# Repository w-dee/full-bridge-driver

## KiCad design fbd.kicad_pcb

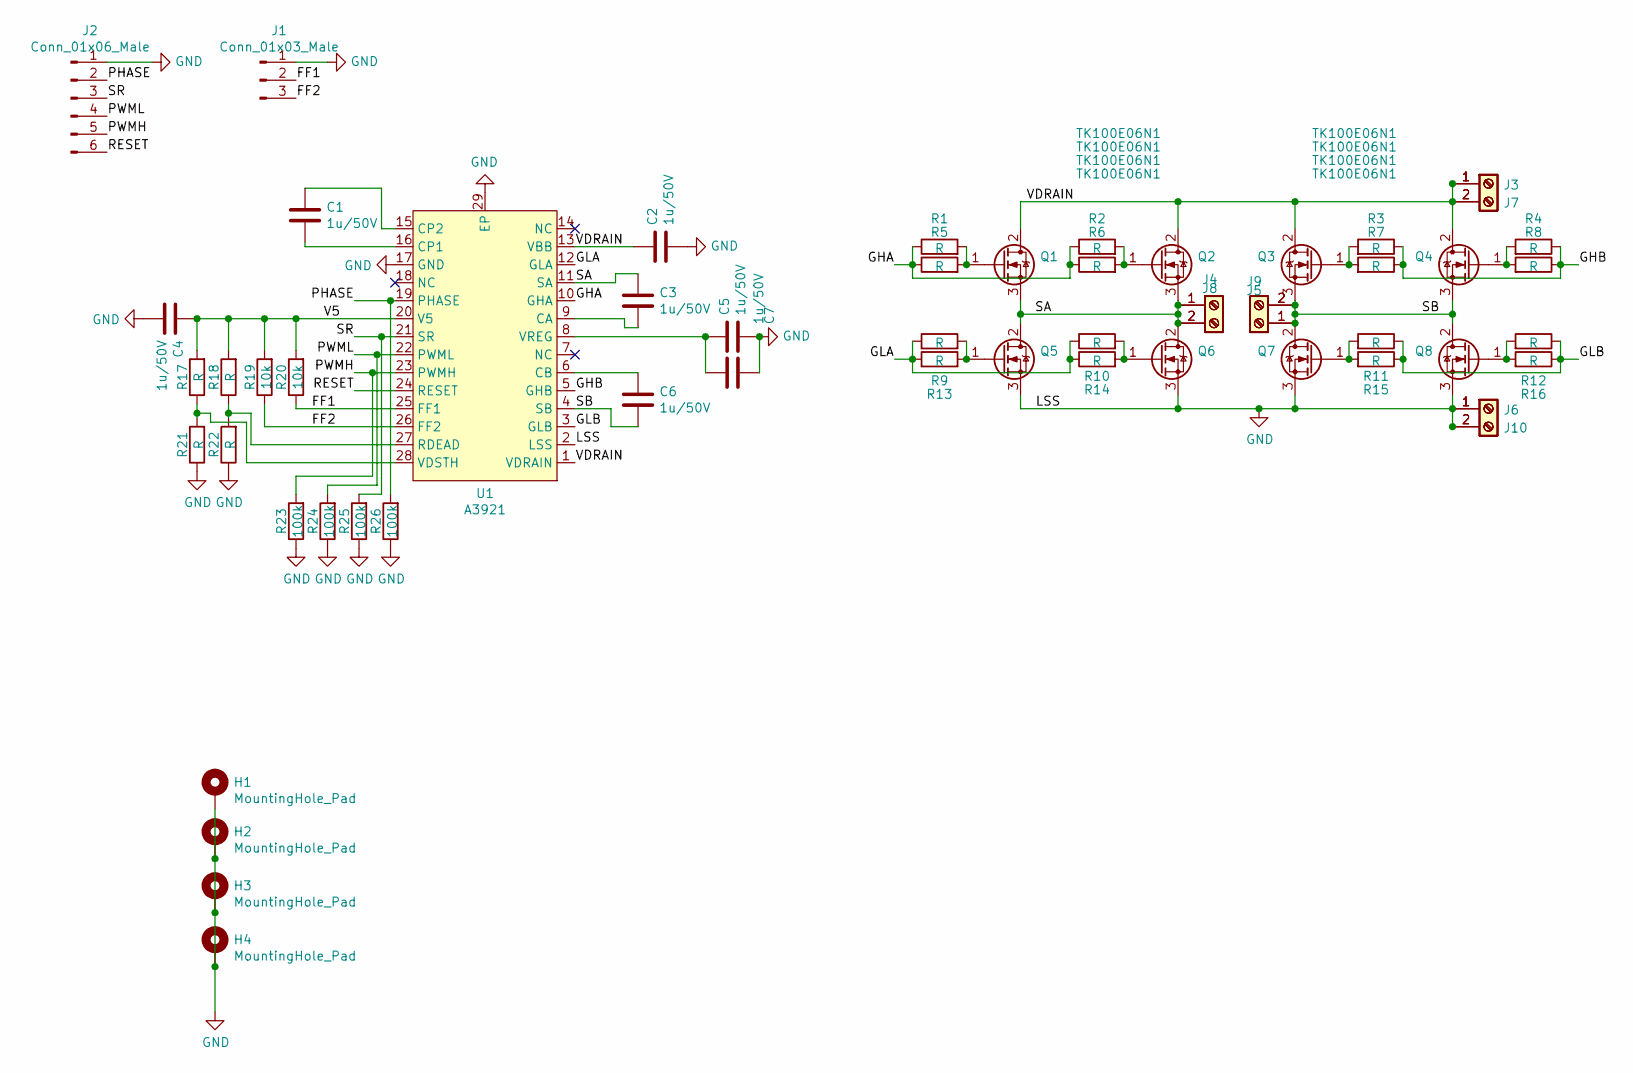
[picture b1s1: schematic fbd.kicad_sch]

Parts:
C1, C2, C3, C4, C5, C6, C7: 1u/50V; R_0603_1608Metric_Pad0.98x0.95mm_HandSolder
H1, H2, H3, H4: MountingHole_Pad; MountingHole_3.2mm_M3
J1: Conn_01x03_Male; JST_XH_B3B-XH-A_1x03_P2.50mm_Vertical
J2: Conn_01x06_Male; JST_XH_B6B-XH-A_1x06_P2.50mm_Vertical
J3, J4, J5, J6, J7, J8, J9, J10: Screw_Terminal_01x02; Terminal-Block-7.62mm-20A-300V
Q1, Q2, Q3, Q4, Q5, Q6, Q7, Q8: TK100E06N1; TO-252-3_Heatsink-TO220-Compat
R1, R2, R3, R4, R5, R6, R7, R8, R9, R10, R11, R12, R13, R14, R15, R16, R17, R18, R21, R22: R; R_0603_1608Metric_Pad0.98x0.95mm_HandSolder
R19, R20: 10k; R_0603_1608Metric_Pad0.98x0.95mm_HandSolder
R23, R24, R25, R26: 100k; R_0603_1608Metric_Pad0.98x0.95mm_HandSolder
U1: A3921; TSSOP-28-1EP_4.4x9.7mm-pin-width6.1_P0.65mm

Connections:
/FF1: J1.2, R20.1, U1.25 (FF1)
/FF2: J1.3, R19.1, U1.26 (FF2)
/GHA: R1.1, R2.1, R5.1, R6.1, U1.10 (GHA)
/GHB: R3.1, R4.1, R7.1, R8.1, U1.5 (GHB)
/GLA: R9.1, R10.1, R13.1, R14.1, U1.12 (GLA)
/GLB: R11.1, R12.1, R15.1, R16.1, U1.3 (GLB)
/PHASE: J2.2, R26.2, U1.19 (PHASE)
/PWMH: J2.5, R23.2, U1.23 (PWMH)
/PWML: J2.4, R24.2, U1.22 (PWML)
/RESET: J2.6, U1.24 (RESET)
/SA: C3.1, J4.1, J4.2, J8.1, J8.2, Q1.3 (S), Q2.3 (S), Q5.2 (D), Q6.2 (D), U1.11 (SA)
/SB: C6.2, J5.1, J5.2, J9.1, J9.2, Q3.3 (S), Q4.3 (S), Q7.2 (D), Q8.2 (D), U1.4 (SB)
/SR: J2.3, R25.2, U1.21 (SR)
/V5: C4.1, R17.2, R18.2, R19.2, R20.2, U1.20 (V5)
/VDRAIN: C2.1, J3.1, J3.2, J7.1, J7.2, Q1.2 (D), Q2.2 (D), Q3.2 (D), Q4.2 (D), U1.1 (VDRAIN), U1.13 (VBB)
GND: C2.2, C4.2, C5.2, C7.2, H1.1, H2.1, H3.1, H4.1, J1.1, J2.1, J6.1, J6.2, J10.1, J10.2, Q5.3 (S), Q6.3 (S), Q7.3 (S), Q8.3 (S), R21.1, R22.1, R23.1, R24.1, R25.1, R26.1, U1.2 (LSS), U1.17 (GND), U1.29 (EP)
unnamed: C1.1, U1.15 (CP2)
unnamed: C1.2, U1.16 (CP1)
unnamed: C3.2, U1.9 (CA)
unnamed: C5.1, C7.1, U1.8 (VREG)
unnamed: C6.1, U1.6 (CB)
unnamed: Q1.1 (G), R1.2, R5.2
unnamed: Q2.1 (G), R2.2, R6.2
unnamed: Q3.1 (G), R3.2, R7.2
unnamed: Q4.1 (G), R4.2, R8.2
unnamed: Q5.1 (G), R9.2, R13.2
unnamed: Q6.1 (G), R10.2, R14.2
unnamed: Q7.1 (G), R11.2, R15.2
unnamed: Q8.1 (G), R12.2, R16.2
unnamed: R17.1, R21.2, U1.28 (VDSTH)
unnamed: R18.1, R22.2, U1.27 (RDEAD)

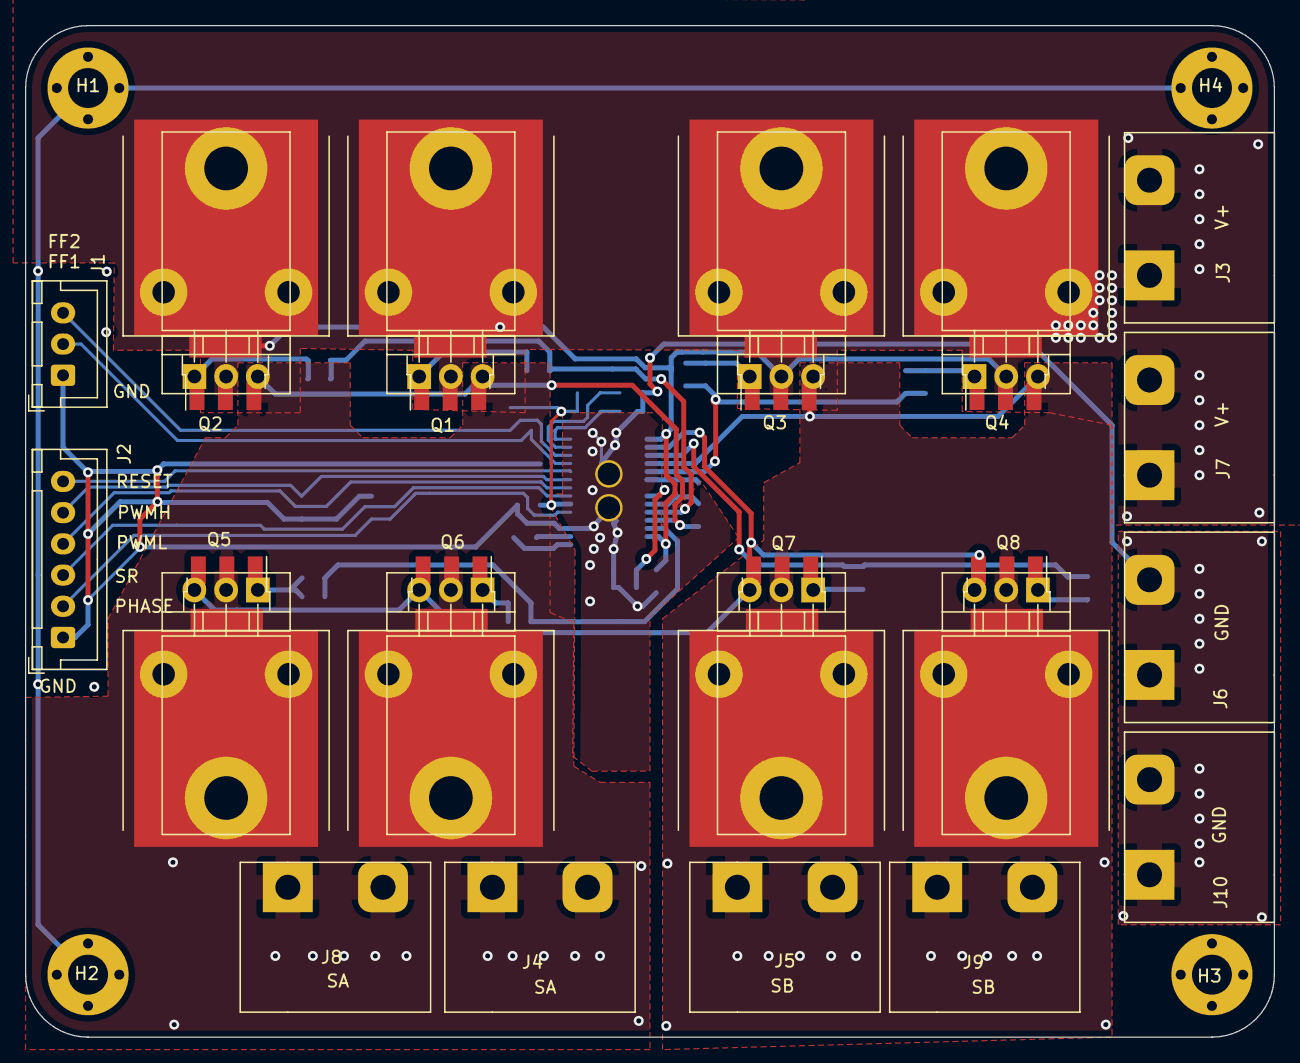
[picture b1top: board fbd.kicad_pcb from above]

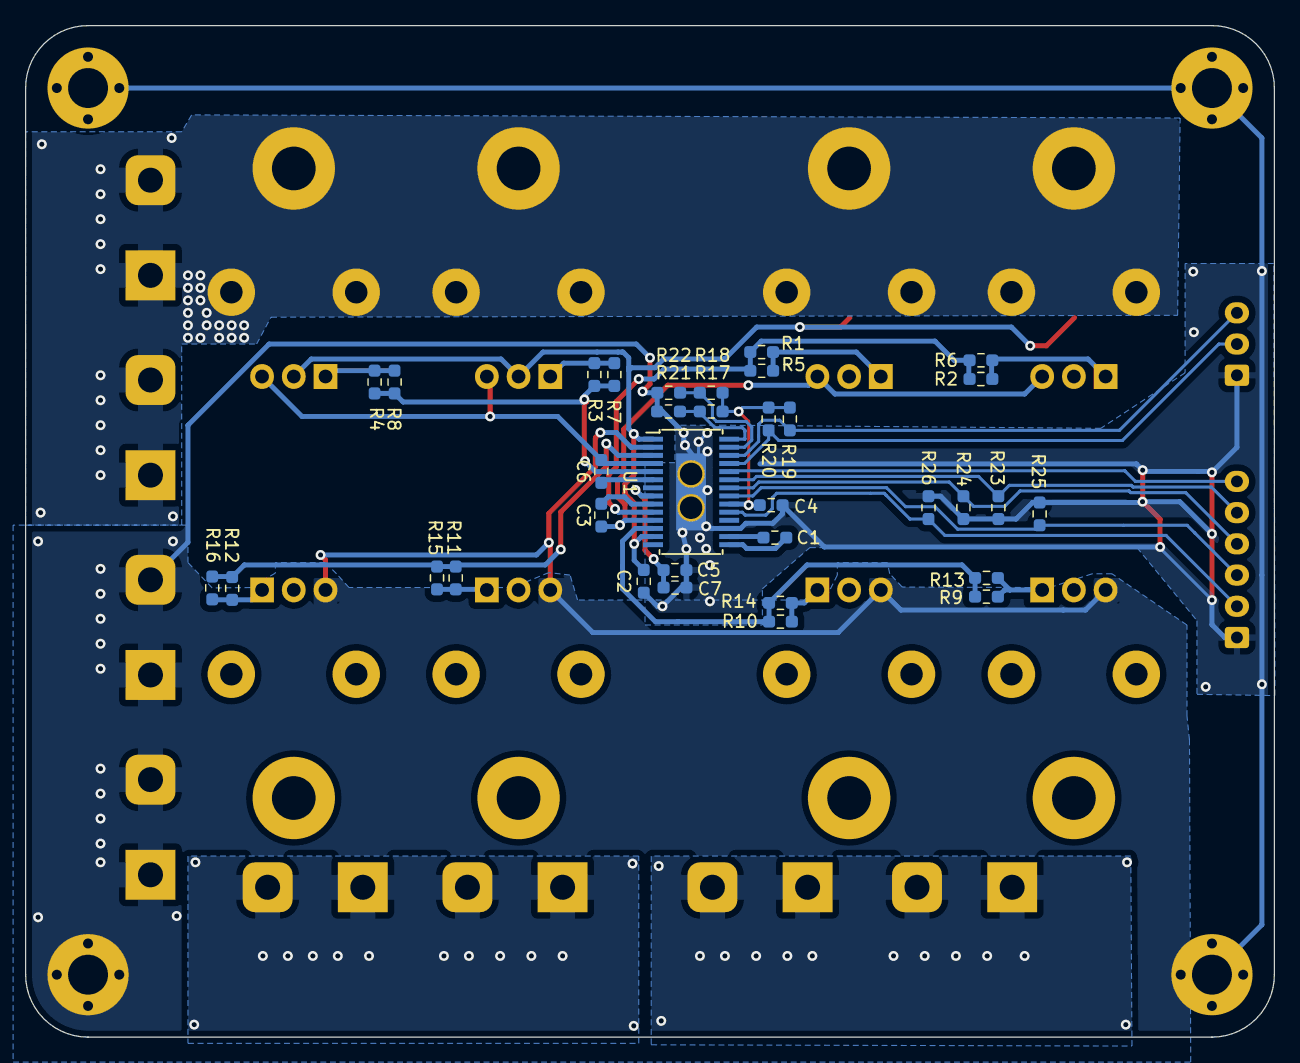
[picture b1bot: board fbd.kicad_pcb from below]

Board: 2 copper layers, 100.0 x 81.0 mm, 56 parts (34 on the bottom side), 31 nets.
